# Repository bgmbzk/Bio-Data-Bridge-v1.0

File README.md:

# Bio-Data-Bridge v1.0 🩺💻

**Bio-Data-Bridge**, insan vücudundan alınan hassas biyometrik sinyalleri (EKG, EMG veya diğer analog veriler) güvenli bir şekilde işlemek ve dijital ortama aktarmak için tasarlanmış, yüksek izolasyonlu bir **Biyometrik Veri Arayüzüdür**.

## 🚀 Projenin Amacı ve Kapsamı
Bu projenin temel odağı, insan vücudundan gelen mikrovolt seviyesindeki zayıf analog sinyallerin, dış gürültüden arındırılarak ve **elektriksel güvenlikten ödün vermeden** bilgisayara aktarılmasıdır. 

* **İnsan-Makine Arayüzü (HMI):** Kart üzerindeki özel konnektör yapısı, elektrotlar aracılığıyla doğrudan insan vücudundan veri alacak şekilde konfigüre edilmiştir.
* **Kullanıcı Güvenliği:** Kullanıcı ile doğrudan fiziksel temas olduğu için sistem, **PC817 optokuplörler** kullanılarak bilgisayarın şebeke geriliminden ve olası voltaj dalgalanmalarından tamamen izole edilmiştir.

## 🛠 Teknik Sinyal Hattı (Signal Chain)
1.  **Veri Toplama:** İnsan vücudundan gelen analog sinyaller ana giriş konnektörü üzerinden sisteme dahil olur.
2.  **Sinyal İşleme:** Mikrovolt seviyesindeki veriler, **LM358 Op-Amp** katmanında filtrelenir ve işlenebilir seviyeye yükseltilir.
3.  **İzolasyon ve Aktarım:** İşlenen veri, elektriksel izolasyon bariyerini geçerek **CH340G** USB-UART köprüsü üzerinden bilgisayara iletilir.
4.  **Kontrol:** Tüm süreç endüstri standardı **ATmega328P** mikrodenetleyicisi tarafından yönetilir.

## 📐 PCB Tasarım Özellikleri
* **Güvenlik Odaklı Layout:** İzolasyon bariyeri (Clearance/Creepage), kullanıcı güvenliğini en üst düzeyde tutacak şekilde tasarlanmıştır.
* **Özel Geometri:** Ergonomik kullanım ve estetik bir görünüm için **özel pahlı (chamfered)** kenar kesimi uygulanmıştır.
* **Sinyal Bütünlüğü:** Hassas analog hatlar, dijital gürültüden (EMI) korunması için PCB üzerinde optimize edilmiştir.
* **GND Copper Pour (Topraklama Alanı):** Sinyal bütünlüğünü artırmak ve gürültüyü minimize etmek amacıyla PCB'nin hem ön (F.Cu) hem de arka (B.Cu) yüzeyine geniş bakır alanlar (Copper Pour) eklenerek tüm toprak hatları optimize edilmiştir.

## 📁 Klasör İçeriği & Dokümantasyon
* `/Gerbers`: Fabrikasyon için hazır üretim (Gerber & Drill) dosyaları.
* `/Schematic`: Devre şeması ve tasarım detayları.
* **`Bio-Data-Bridge.csv` (BOM Listesi):** Projenin montajı için gereken tüm elektronik bileşenlerin (direnç, kapasitör, IC vb.) tam listesi, değerleri ve kılıf (footprint) bilgileri.
* `Bio-Data-Bridge.png`: Kartın 3D render görseli.

---

### 🛠 Kurulum ve Üretim
1.  **PCB Üretimi:** `Gerber` klasöründeki dosyaları herhangi bir PCB üreticisine gönderin.
2.  **Malzeme Tedariği:** `Bio-Data-Bridge.csv` dosyasını açarak gerekli tüm parçaları (BOM listesi) temin edin.
3.  **Montaj:** Şematik ve PCB layout takibiyle bileşenleri lehimleyin.
4.  **Veri Akışı:** USB üzerinden bağlantı kurarak biyometrik veri akışını izlemeye başlayın.

---
*Bu proje KiCad 8.0 kullanılarak geliştirilmiştir.*

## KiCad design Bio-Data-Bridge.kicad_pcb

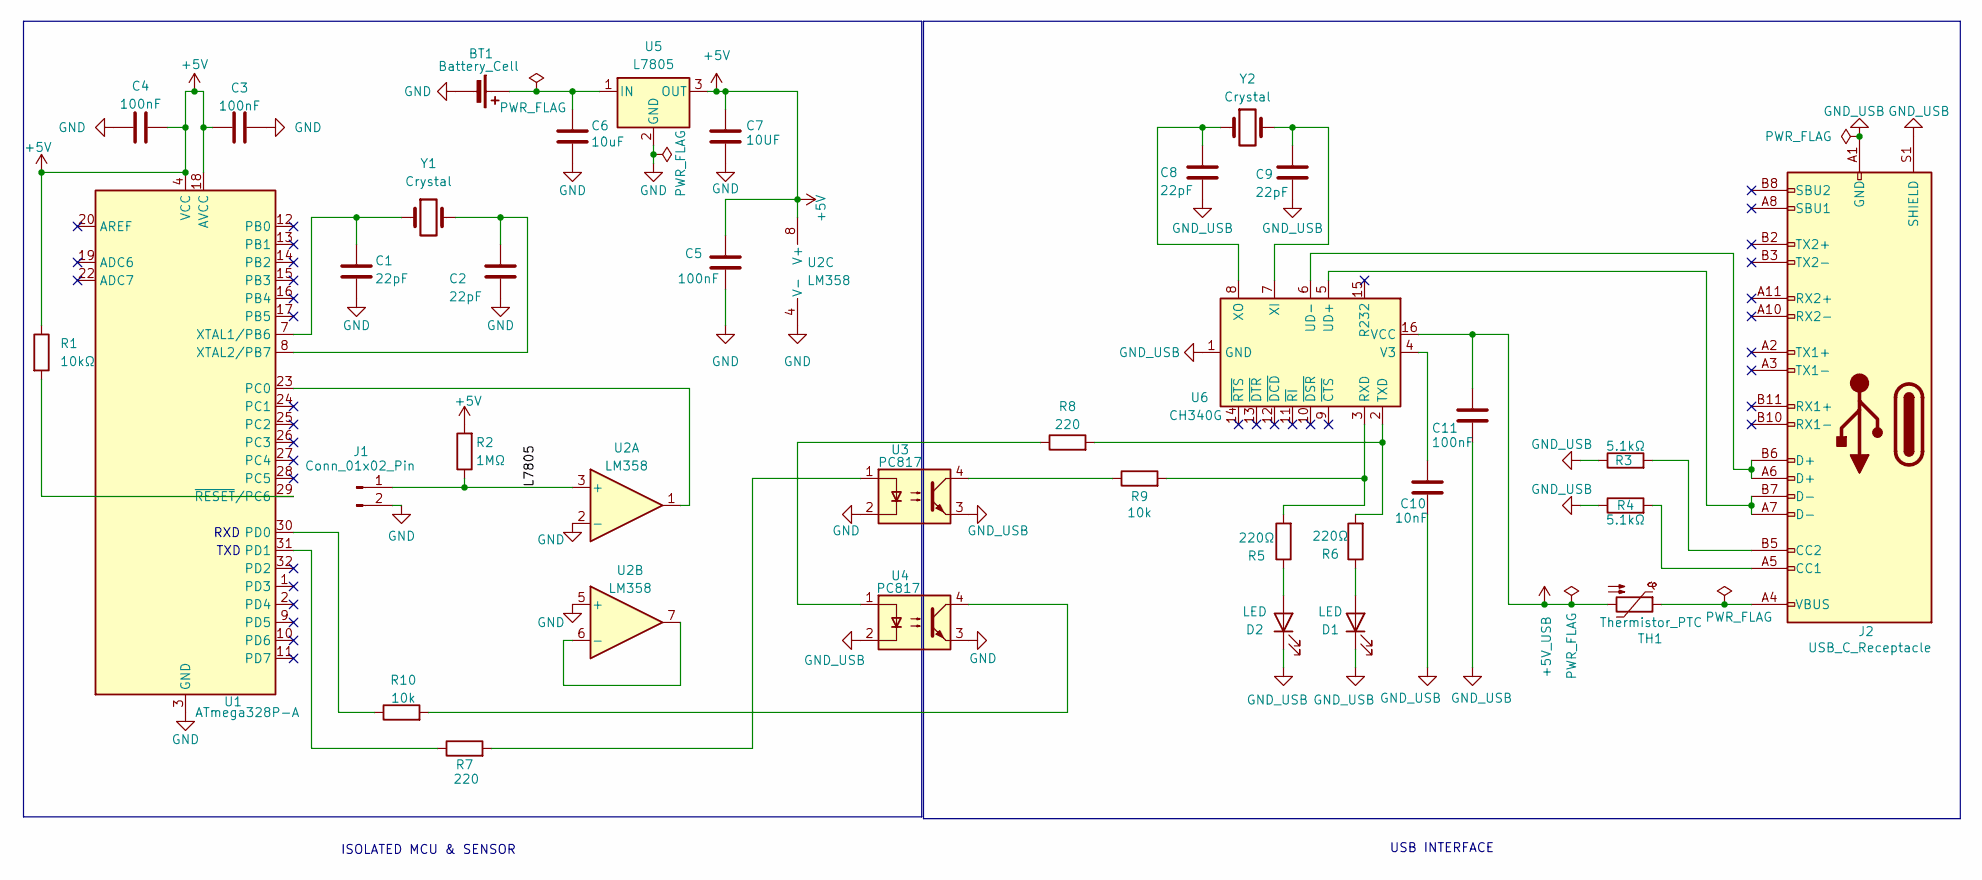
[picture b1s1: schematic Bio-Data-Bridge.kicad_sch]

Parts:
BT1: Battery_Cell; PinHeader_1x02_P2.54mm_Vertical
C1, C2, C8, C9: 22pF; C_0805_2012Metric
C3, C4, C5, C11: 100nF; C_0805_2012Metric
C6: 10uF; C_0805_2012Metric
C7: 10UF; C_0805_2012Metric
C10: 10nF; C_0805_2012Metric
D1, D2: LED; LED_0805_2012Metric
J1: Conn_01x02_Pin; PinHeader_1x02_P2.54mm_Vertical
J2: USB_C_Receptacle; USB_C_Receptacle_HRO_TYPE-C-31-M-12
R1: 10kΩ; R_0805_2012Metric
R2: 1MΩ; R_0805_2012Metric
R3, R4: 5.1kΩ; R_0805_2012Metric
R5, R6: 220Ω; R_0805_2012Metric
R7, R8: 220; R_0805_2012Metric
R9, R10: 10k; R_0805_2012Metric
TH1: Thermistor_PTC; Fuse_0805_2012Metric
U1: ATmega328P-A; TQFP-32_7x7mm_P0.8mm
U2: LM358; SOIC-8_3.9x4.9mm_P1.27mm
U3, U4: PC817; SMDIP-4_W7.62mm
U5: L7805; SOT-223-3_TabPin2
U6: CH340G; SOIC-16_3.9x9.9mm_P1.27mm
Y1, Y2: Crystal; Crystal_SMD_5032-2Pin_5.0x3.2mm

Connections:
+5V: C3.1, C4.2, C5.1, C7.1, R1.1, R2.2, U1.4 (VCC), U1.6 (VCC), U1.18 (AVCC), U2.8 (V+), U5.3 (OUT)
+5V_USB: C11.1, TH1.2, U6.16 (VCC)
/L7805: J1.1, R2.1, U2.3 (+)
GND: BT1.2 (-), C1.2, C2.2, C3.2, C4.1, C5.2, C6.2, C7.2, J1.2, U1.3 (GND), U1.5 (GND), U1.21 (GND), U2.2 (-), U2.4 (V-), U2.5 (+), U3.2, U4.3, U5.2 (GND)
GND_USB: C8.2, C9.2, C10.1, C11.2, D1.1 (K), D2.1 (K), J2.A1 (GND), J2.A12 (GND), J2.B1 (GND), J2.B12 (GND), J2.S1 (SHIELD), R3.1, R4.1, U3.3, U4.2, U6.1 (GND)
unnamed: BT1.1 (+), C6.1, U5.1 (IN)
unnamed: D1.2 (A), R6.1
unnamed: D2.2 (A), R5.1
unnamed: J2.A5 (CC1), R4.2
unnamed: J2.B5 (CC2), R3.2
unnamed: J2.A4 (VBUS), J2.A9 (VBUS), J2.B4 (VBUS), J2.B9 (VBUS), TH1.1
unnamed: R7.2, U3.1
unnamed: R8.1, U4.1
unnamed: R9.1, U3.4
unnamed: R10.2, U4.4
unnamed: U1.23 (PC0), U2.1
unnamed: R10.1, U1.30 (PD0)
unnamed: R7.1, U1.31 (PD1)
unnamed: C1.1, U1.7 (XTAL1/PB6), Y1.1
unnamed: C2.1, U1.8 (XTAL2/PB7), Y1.2
unnamed: R1.2, U1.29 (~RESET/PC6)
unnamed: U2.6 (-), U2.7
unnamed: R5.2, R9.2, U6.3 (RXD)
unnamed: R6.2, R8.2, U6.2 (TXD)
unnamed: J2.A7 (D-), J2.B7 (D-), U6.5 (UD+)
unnamed: J2.A6 (D+), J2.B6 (D+), U6.6 (UD-)
unnamed: C10.2, U6.4 (V3)
unnamed: C9.1, U6.7 (XI), Y2.2
unnamed: C8.1, U6.8 (XO), Y2.1

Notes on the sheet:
ISOLATED MCU & SENSOR
RXD
USB INTERFACE
TXD

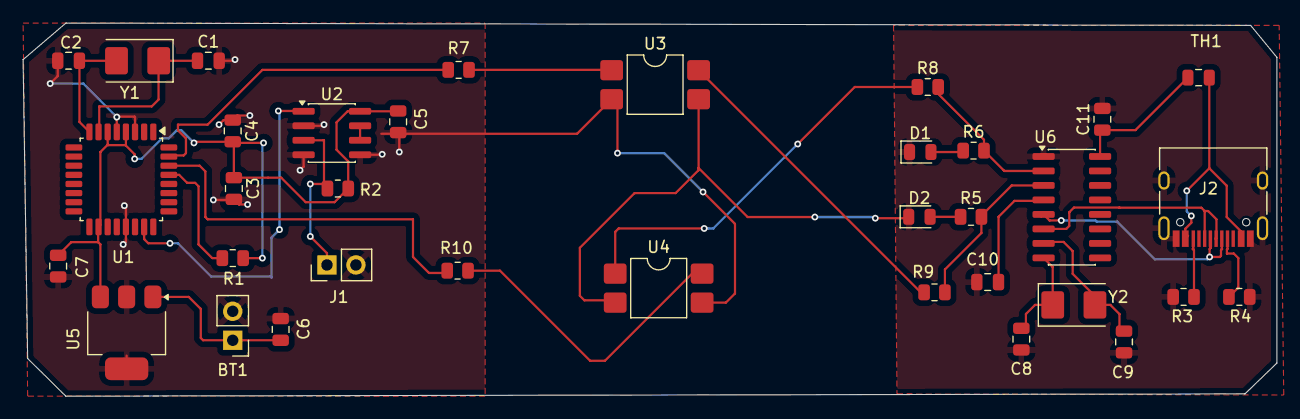
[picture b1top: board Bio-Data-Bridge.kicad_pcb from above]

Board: 2 copper layers, 109.9 x 32.7 mm, 35 parts (0 on the bottom side), 29 nets.

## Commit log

2026-04-08 Add README for Bio-Data-Bridge project
    This README introduces the Bio-Data-Bridge project, detailing its purpose, technical specifications, and installation instructions.
2026-04-08 Add GND Copper Pour details to README
